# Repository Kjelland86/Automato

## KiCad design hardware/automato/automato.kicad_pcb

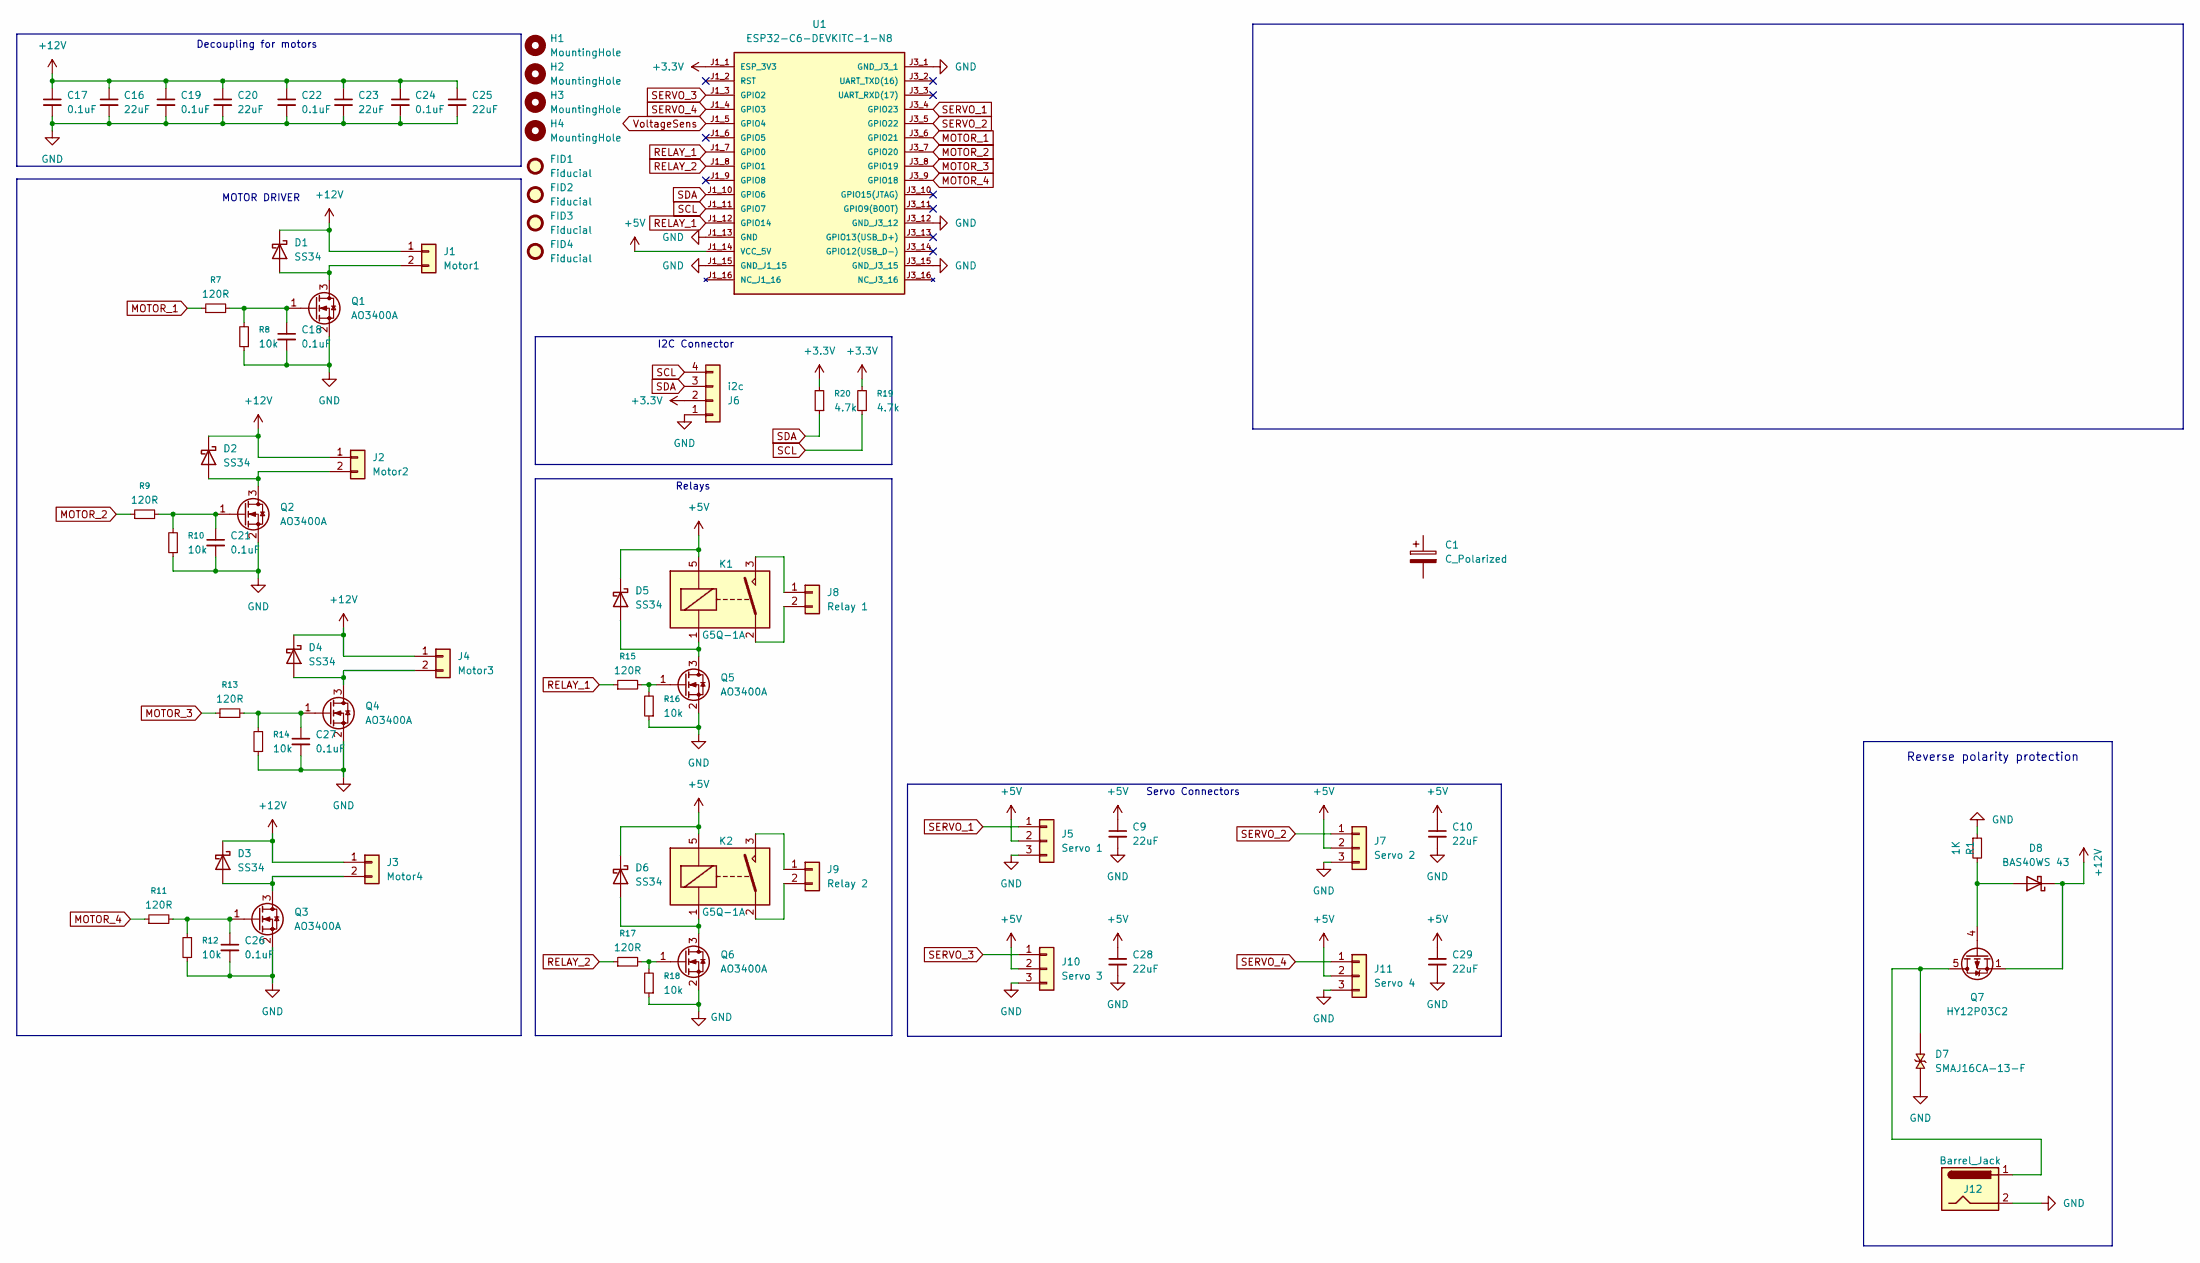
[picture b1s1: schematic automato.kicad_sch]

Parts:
C1: C_Polarized
C9, C10, C16, C20, C23, C25, C28, C29: 22uF; C_0805_2012Metric
C17, C18, C19, C21, C22, C24, C26, C27: 0.1uF; C_0603_1608Metric
D1, D2, D3, D4, D5, D6: SS34; D_SMA
D7: SMAJ16CA-13-F; DIOM4325X250N; PARTREV S2102
D8: BAS40WS 43; D_SOD-323
FID1, FID2, FID3, FID4: Fiducial; Fiducial_1.5mm_Mask3mm
H1, H2, H3, H4: MountingHole; MountingHole_3.2mm_M3
J1: Motor1; TerminalBlock_Phoenix_MKDS-1,5-2-5.08_1x02_P5.08mm_Horizont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
J2: Motor2; TerminalBlock_Phoenix_MKDS-1,5-2-5.08_1x02_P5.08mm_Horizont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
J3: Motor4; TerminalBlock_Phoenix_MKDS-1,5-2-5.08_1x02_P5.08mm_Horizont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
J4: Motor3; TerminalBlock_Phoenix_MKDS-1,5-2-5.08_1x02_P5.08mm_Horizont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
J5: Servo 1; PinHeader_1x03_P2.54mm_Vertical
J6: i2c; JST_PH_S4B-PH-K_1x04_P2.00mm_Horizontal
J7: Servo 2; PinHeader_1x03_P2.54mm_Vertical
J8: Relay 1; TerminalBlock_Phoenix_MKDS-1,5-2-5.08_1x02_P5.08mm_Horizont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
J9: Relay 2; TerminalBlock_Phoenix_MKDS-1,5-2-5.08_1x02_P5.08mm_Horizont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
J10: Servo 3; PinHeader_1x03_P2.54mm_Vertical
J11: Servo 4; PinHeader_1x03_P2.54mm_Vertical
J12: Barrel_Jack; BarrelJack_Horizontal
K1, K2: G5Q-1A; Relay_SPST_Omron-G5Q-1A
Q1, Q2, Q3, Q4, Q5, Q6: AO3400A; SOT-23
Q7: HY12P03C2; PowerPAK_SO-8_Single
R1: 1K; R_0402_1005Metric
R7, R9, R11, R13, R15, R17: 120R; R_0603_1608Metric
R8, R10, R12, R14, R16, R18: 10k; R_0603_1608Metric
R19, R20: 4.7k; R_0603_1608Metric
U1: ESP32-C6-DEVKITC-1-N8; MODULE_ESP32-C6-DEVKITC-1-N8; PARTREV 1.3

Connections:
+3.3V: J6.2, R19.2, R20.2, U1.J1_1 (ESP_3V3); also elsewhere on the board
+5V: C9.1, C10.1, C28.1, C29.1, D5.1 (K), D6.1 (K), J5.2, J7.2, J10.2, J11.2, K1.5, K2.5, U1.J1_14 (VCC_5V); also elsewhere on the board
+12V: C16.1, C17.1, C19.1, C20.1, C22.1, C23.1, C24.1, C25.1, D1.1 (K), D2.1 (K), D3.1 (K), D4.1 (K), D8.1 (K), J1.1, J2.1, J3.1, J4.1, Q7.1 (S), Q7.2 (S), Q7.3 (S); also elsewhere on the board
GND: C9.2, C10.2, C16.2, C17.2, C18.2, C19.2, C20.2, C21.2, C22.2, C23.2, C24.2, C25.2, C26.2, C27.2, C28.2, C29.2, D7.1, J5.3, J6.1, J7.3, J10.3, J11.3, J12.2, Q1.2 (S), Q2.2 (S), Q3.2 (S), Q4.2 (S), Q5.2 (S), Q6.2 (S), R1.1, R8.1, R10.1, R12.1, R14.1, R16.1, R18.1, U1.J1_13 (GND), U1.J1_15 (GND_J1_15), U1.J3_1 (GND_J3_1), U1.J3_12 (GND_J3_12), U1.J3_15 (GND_J3_15); also elsewhere on the board
MOTOR_1: R7.1, U1.J3_6 (GPIO21)
MOTOR_2: R9.1, U1.J3_7 (GPIO20)
MOTOR_3: R13.1, U1.J3_8 (GPIO19)
MOTOR_4: R11.1, U1.J3_9 (GPIO18)
unnamed: D1.2 (A), J1.2, Q1.3 (D)
unnamed: D2.2 (A), J2.2, Q2.3 (D)
unnamed: D3.2 (A), J3.2, Q3.3 (D)
unnamed: D4.2 (A), J4.2, Q4.3 (D)
unnamed: D5.2 (A), K1.1, Q5.3 (D)
unnamed: D6.2 (A), K2.1, Q6.3 (D)
unnamed: D8.2 (A), Q7.4 (G), R1.2
unnamed: J8.1, K1.3
unnamed: J8.2, K1.2
unnamed: J9.1, K2.3
unnamed: J9.2, K2.2
unnamed 19: D7.2, J12.1, Q7.5 (D); also elsewhere on the board
unnamed: C18.1, Q1.1 (G), R7.2, R8.2
unnamed: C21.1, Q2.1 (G), R9.2, R10.2
unnamed: C26.1, Q3.1 (G), R11.2, R12.2
unnamed: C27.1, Q4.1 (G), R13.2, R14.2
unnamed: Q5.1 (G), R15.2, R16.2
unnamed: Q6.1 (G), R17.2, R18.2
RELAY_1: R15.1, U1.J1_7 (GPIO0), U1.J1_12 (GPIO14)
RELAY_2: R17.1, U1.J1_8 (GPIO1)
SCL: J6.4, R19.1, U1.J1_11 (GPIO7)
SDA: J6.3, R20.1, U1.J1_10 (GPIO6)
SERVO_1: J5.1, U1.J3_4 (GPIO23)
SERVO_2: J7.1, U1.J3_5 (GPIO22)
SERVO_3: J10.1, U1.J1_3 (GPIO2)
SERVO_4: J11.1, U1.J1_4 (GPIO3)
SW1: U1.J1_5 (GPIO4); also elsewhere on the board
SW2: U1.J1_6 (GPIO5); also elsewhere on the board

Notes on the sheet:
Decoupling for motors
MOTOR DRIVER
Relays
Servo Connectors
Reverse polarity protection
I2C Connector

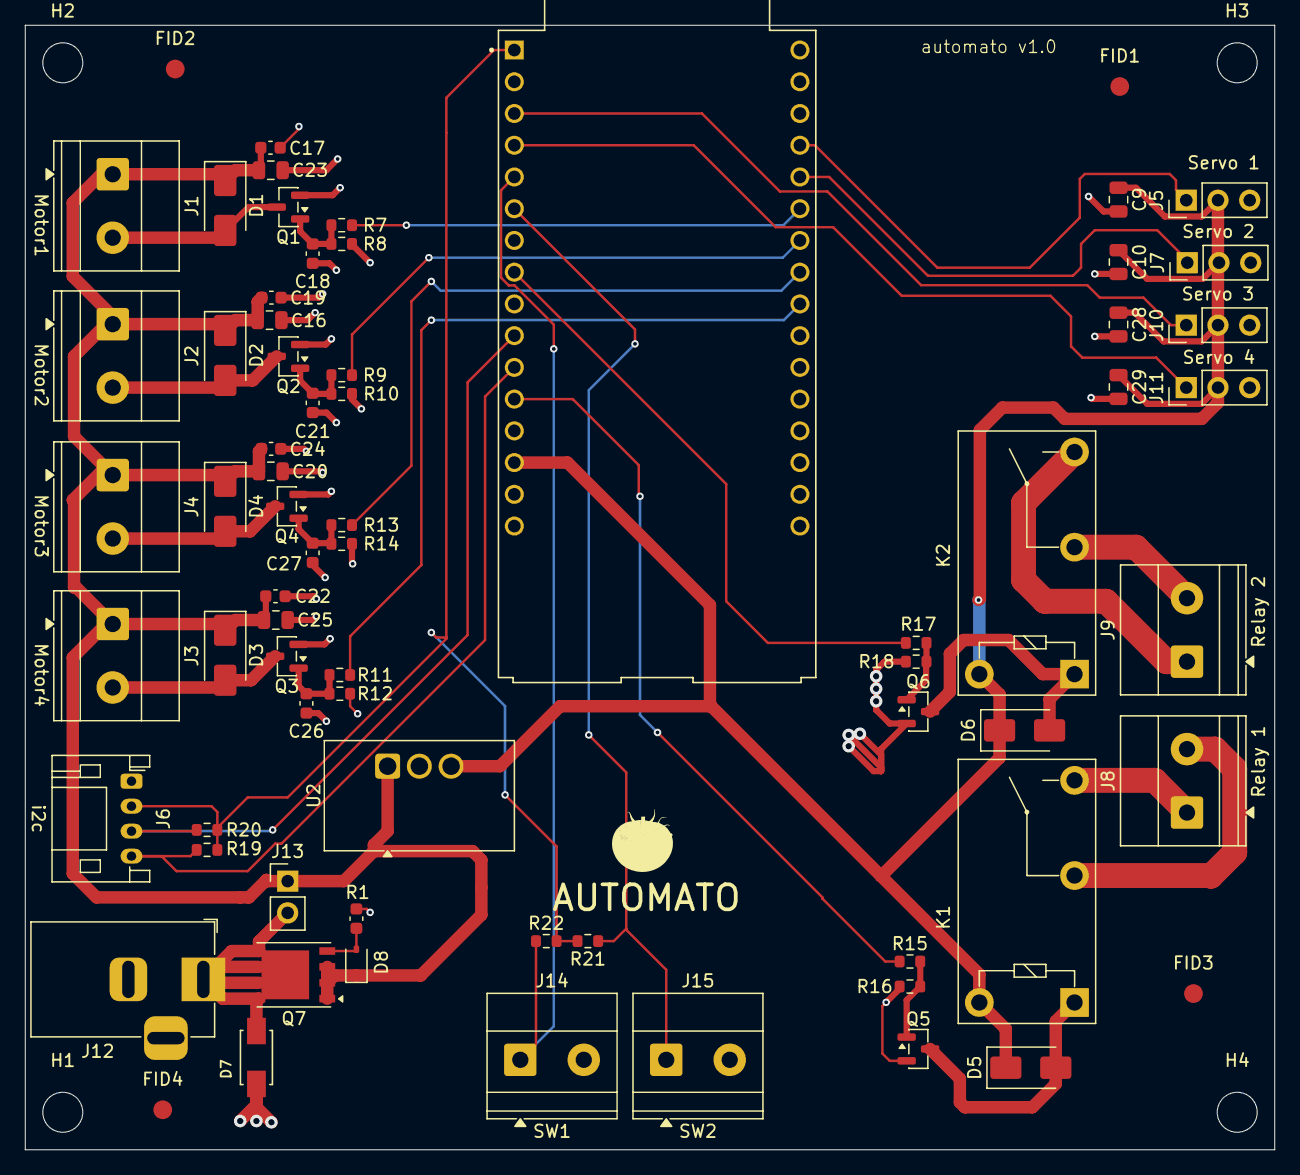
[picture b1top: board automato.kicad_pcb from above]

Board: 2 copper layers, 100.0 x 90.0 mm, 75 parts (0 on the bottom side), 36 nets.

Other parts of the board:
J13: 12V Bypass; PinHeader_1x02_P2.54mm_Vertical
J14: SW1; TerminalBlock_Phoenix_MKDS-1,5-2-5.08_1x02_P5.08mm_Horizont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
J15: SW2; TerminalBlock_Phoenix_MKDS-1,5-2-5.08_1x02_P5.08mm_Horizont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
R21, R22: 10k; R_0603_1608Metric
U2: TSR2-2450N; Converter_DCDC_TRACO_TSR2-24xxN_TSR2-24xxxN_THT

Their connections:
+3.3V: R21.2, R22.2; also elsewhere on the board
+5V: U2.3 (Vout); also elsewhere on the board
+12V: J13.1, U2.1 (Vin); also elsewhere on the board
GND: J14.2, J15.2, U2.2 (GND); also elsewhere on the board
unnamed 19: J13.2; also elsewhere on the board
SW1: J14.1, R22.1; also elsewhere on the board
SW2: J15.1, R21.1; also elsewhere on the board

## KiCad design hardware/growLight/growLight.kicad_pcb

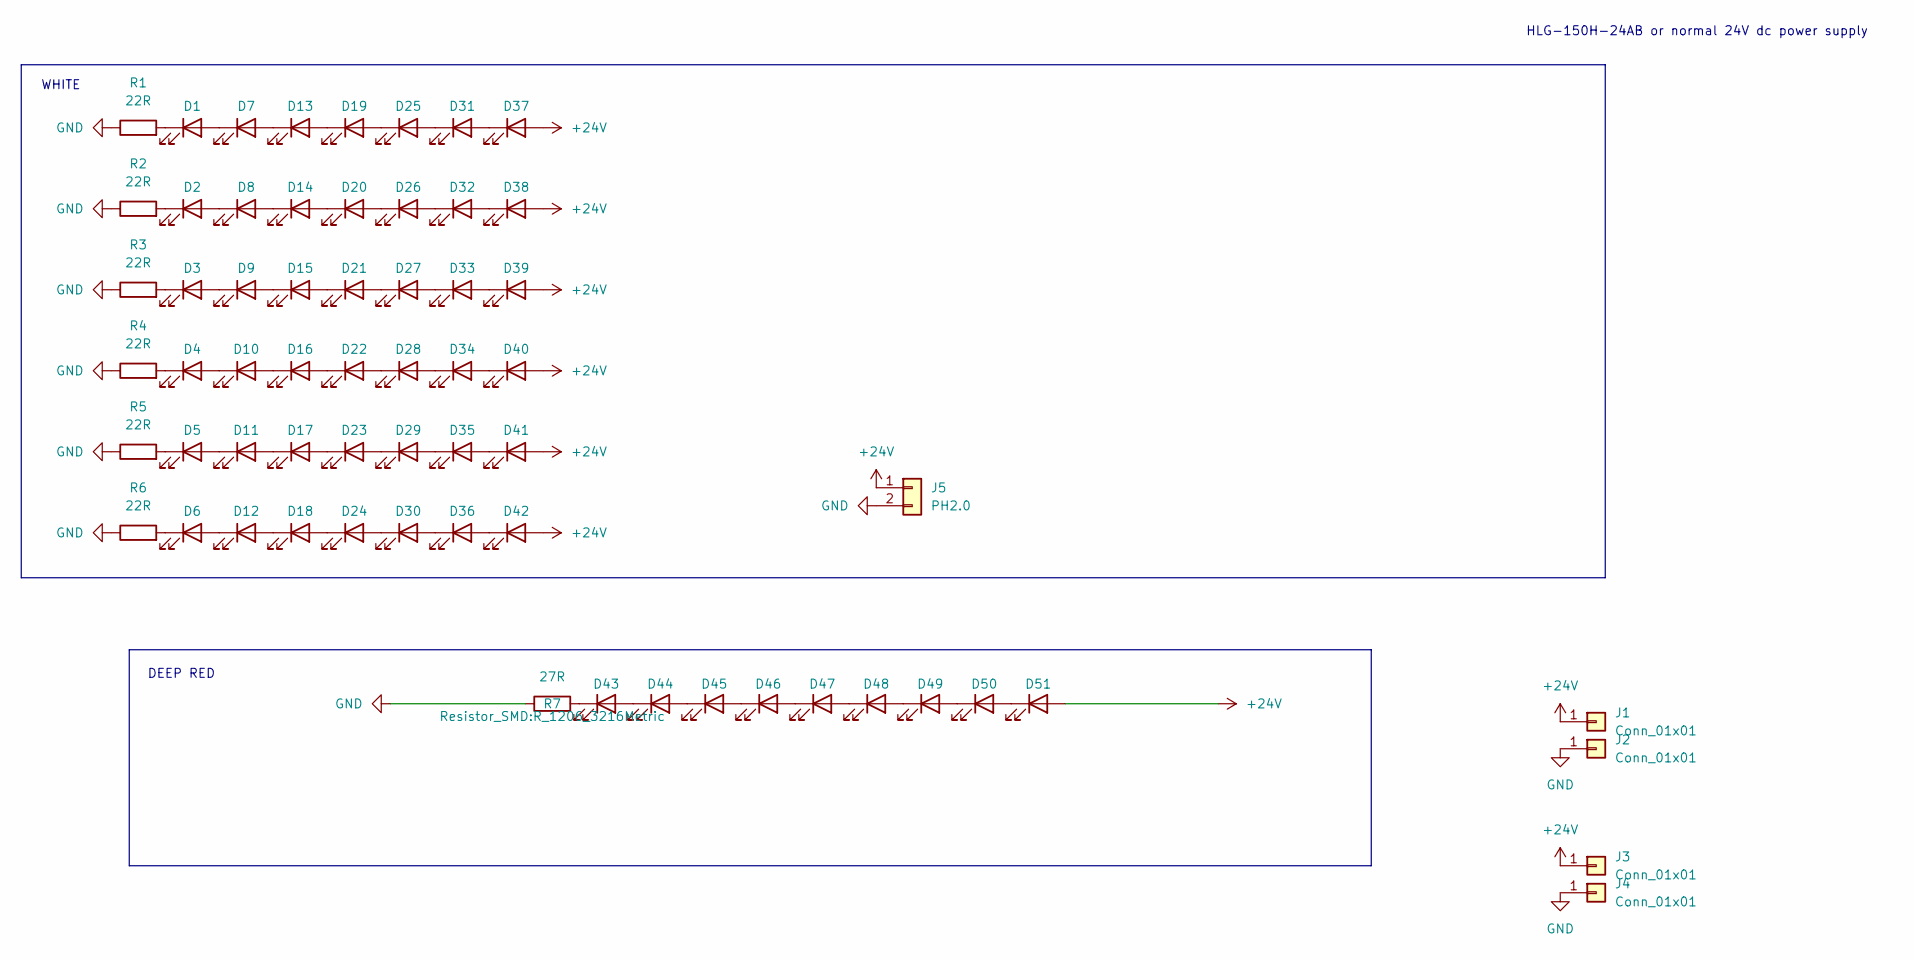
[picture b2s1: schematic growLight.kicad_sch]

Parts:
D1, D2, D3, D4, D5, D6, D7, D8, D9, D10, D11, D12, D13, D14, D15, D16, D17, D18, D19, D20, D21, D22, D23, D24, D25, D26, D27, D28, D29, D30, D31, D32, D33, D34, D35, D36, D37, D38, D39, D40, D41, D42: LED White; LED_PLCC_2835; partnr SPMWH1228FD5WATUVG
D43, D44, D45, D46, D47, D48, D49, D50, D51: LED Deep red; LED_PLCC_2835; partnr 150283HS73103
J1, J2, J3, J4: Conn_01x01; SolderWirePad_1x01_SMD_4x8mm
J5: PH2.0; JST_S2B-PH-SM4-TB
R1, R2, R3, R4, R5, R6: 22R; R_1206_3216Metric
R7: 27R; R_1206_3216Metric

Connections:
+24V: D37.2 (A), D38.2 (A), D39.2 (A), D40.2 (A), D41.2 (A), D42.2 (A), D51.2 (A), J1.1 (Pin_1_1), J3.1 (Pin_1_1), J5.1
GND: J2.1 (Pin_1_1), J4.1 (Pin_1_1), J5.2, R1.1, R2.1, R3.1, R4.1, R5.1, R6.1, R7.1
unnamed: D1.2 (A), D7.1 (K)
unnamed: D1.1 (K), R1.2
unnamed: D2.2 (A), D8.1 (K)
unnamed: D2.1 (K), R2.2
unnamed: D3.2 (A), D9.1 (K)
unnamed: D3.1 (K), R3.2
unnamed: D4.1 (K), R4.2
unnamed: D5.1 (K), R5.2
unnamed: D6.1 (K), R6.2
unnamed: D10.2 (A), D16.1 (K)
unnamed: D4.2 (A), D10.1 (K)
unnamed: D11.2 (A), D17.1 (K)
unnamed: D5.2 (A), D11.1 (K)
unnamed: D12.2 (A), D18.1 (K)
unnamed: D6.2 (A), D12.1 (K)
unnamed: D13.2 (A), D19.1 (K)
unnamed: D7.2 (A), D13.1 (K)
unnamed: D14.2 (A), D20.1 (K)
unnamed: D8.2 (A), D14.1 (K)
unnamed: D15.2 (A), D21.1 (K)
unnamed: D9.2 (A), D15.1 (K)
unnamed: D16.2 (A), D22.1 (K)
unnamed: D17.2 (A), D23.1 (K)
unnamed: D18.2 (A), D24.1 (K)
unnamed: D19.2 (A), D25.1 (K)
unnamed: D20.2 (A), D26.1 (K)
unnamed: D21.2 (A), D27.1 (K)
unnamed: D22.2 (A), D28.1 (K)
unnamed: D23.2 (A), D29.1 (K)
unnamed: D24.2 (A), D30.1 (K)
unnamed: D25.2 (A), D31.1 (K)
unnamed: D26.2 (A), D32.1 (K)
unnamed: D27.2 (A), D33.1 (K)
unnamed: D28.2 (A), D34.1 (K)
unnamed: D29.2 (A), D35.1 (K)
unnamed: D30.2 (A), D36.1 (K)
unnamed: D31.2 (A), D37.1 (K)
unnamed: D32.2 (A), D38.1 (K)
unnamed: D33.2 (A), D39.1 (K)
unnamed: D34.2 (A), D40.1 (K)
unnamed: D35.2 (A), D41.1 (K)
unnamed: D36.2 (A), D42.1 (K)
unnamed: D43.2 (A), D44.1 (K)
unnamed: D43.1 (K), R7.2
unnamed: D44.2 (A), D45.1 (K)
unnamed: D45.2 (A), D46.1 (K)
unnamed: D46.2 (A), D47.1 (K)
unnamed: D47.2 (A), D48.1 (K)
unnamed: D48.2 (A), D49.1 (K)
unnamed: D49.2 (A), D50.1 (K)
unnamed: D50.2 (A), D51.1 (K)

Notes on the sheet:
HLG-150H-24AB or normal 24V dc power supply
WHITE
DEEP RED

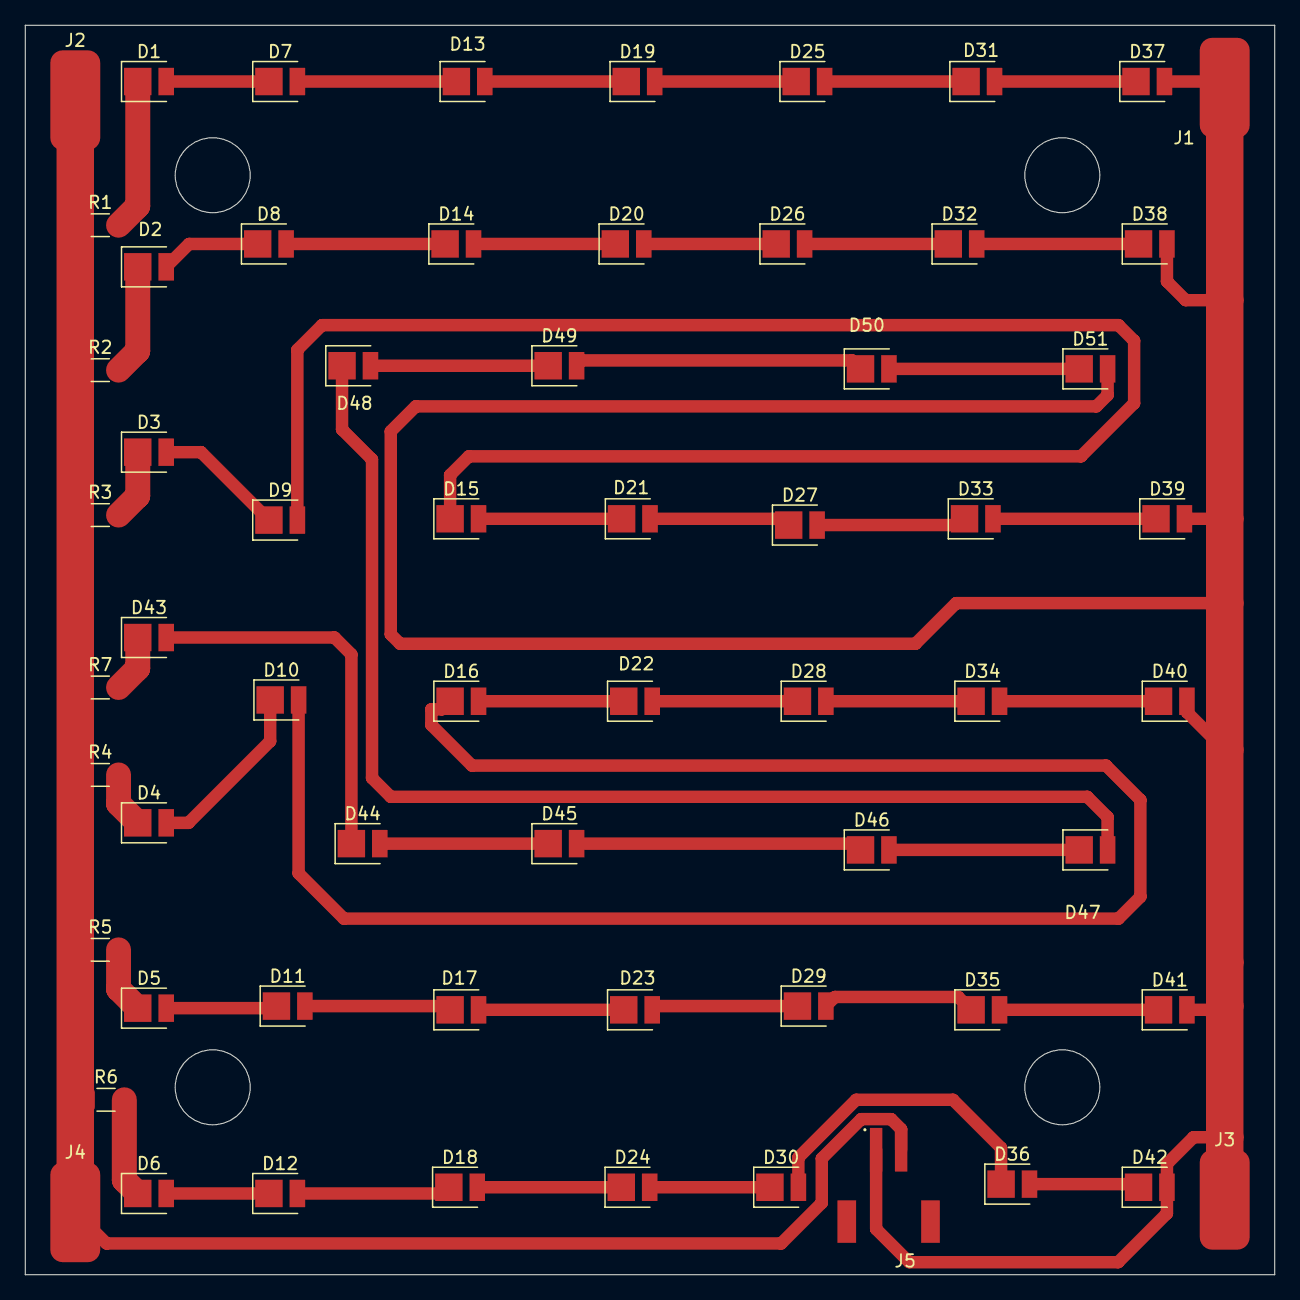
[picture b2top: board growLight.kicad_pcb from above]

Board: 2 copper layers, 100.0 x 100.0 mm, 63 parts (0 on the bottom side), 53 nets.

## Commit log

2026-04-27 create base
2026-04-28 added relays and mosfets
2026-04-29 started layout
2026-04-29 changed 5v power supply
2026-05-04 sent to production
2026-05-27 added growlight
2026-06-10 added drill
2026-06-18 added grow light
